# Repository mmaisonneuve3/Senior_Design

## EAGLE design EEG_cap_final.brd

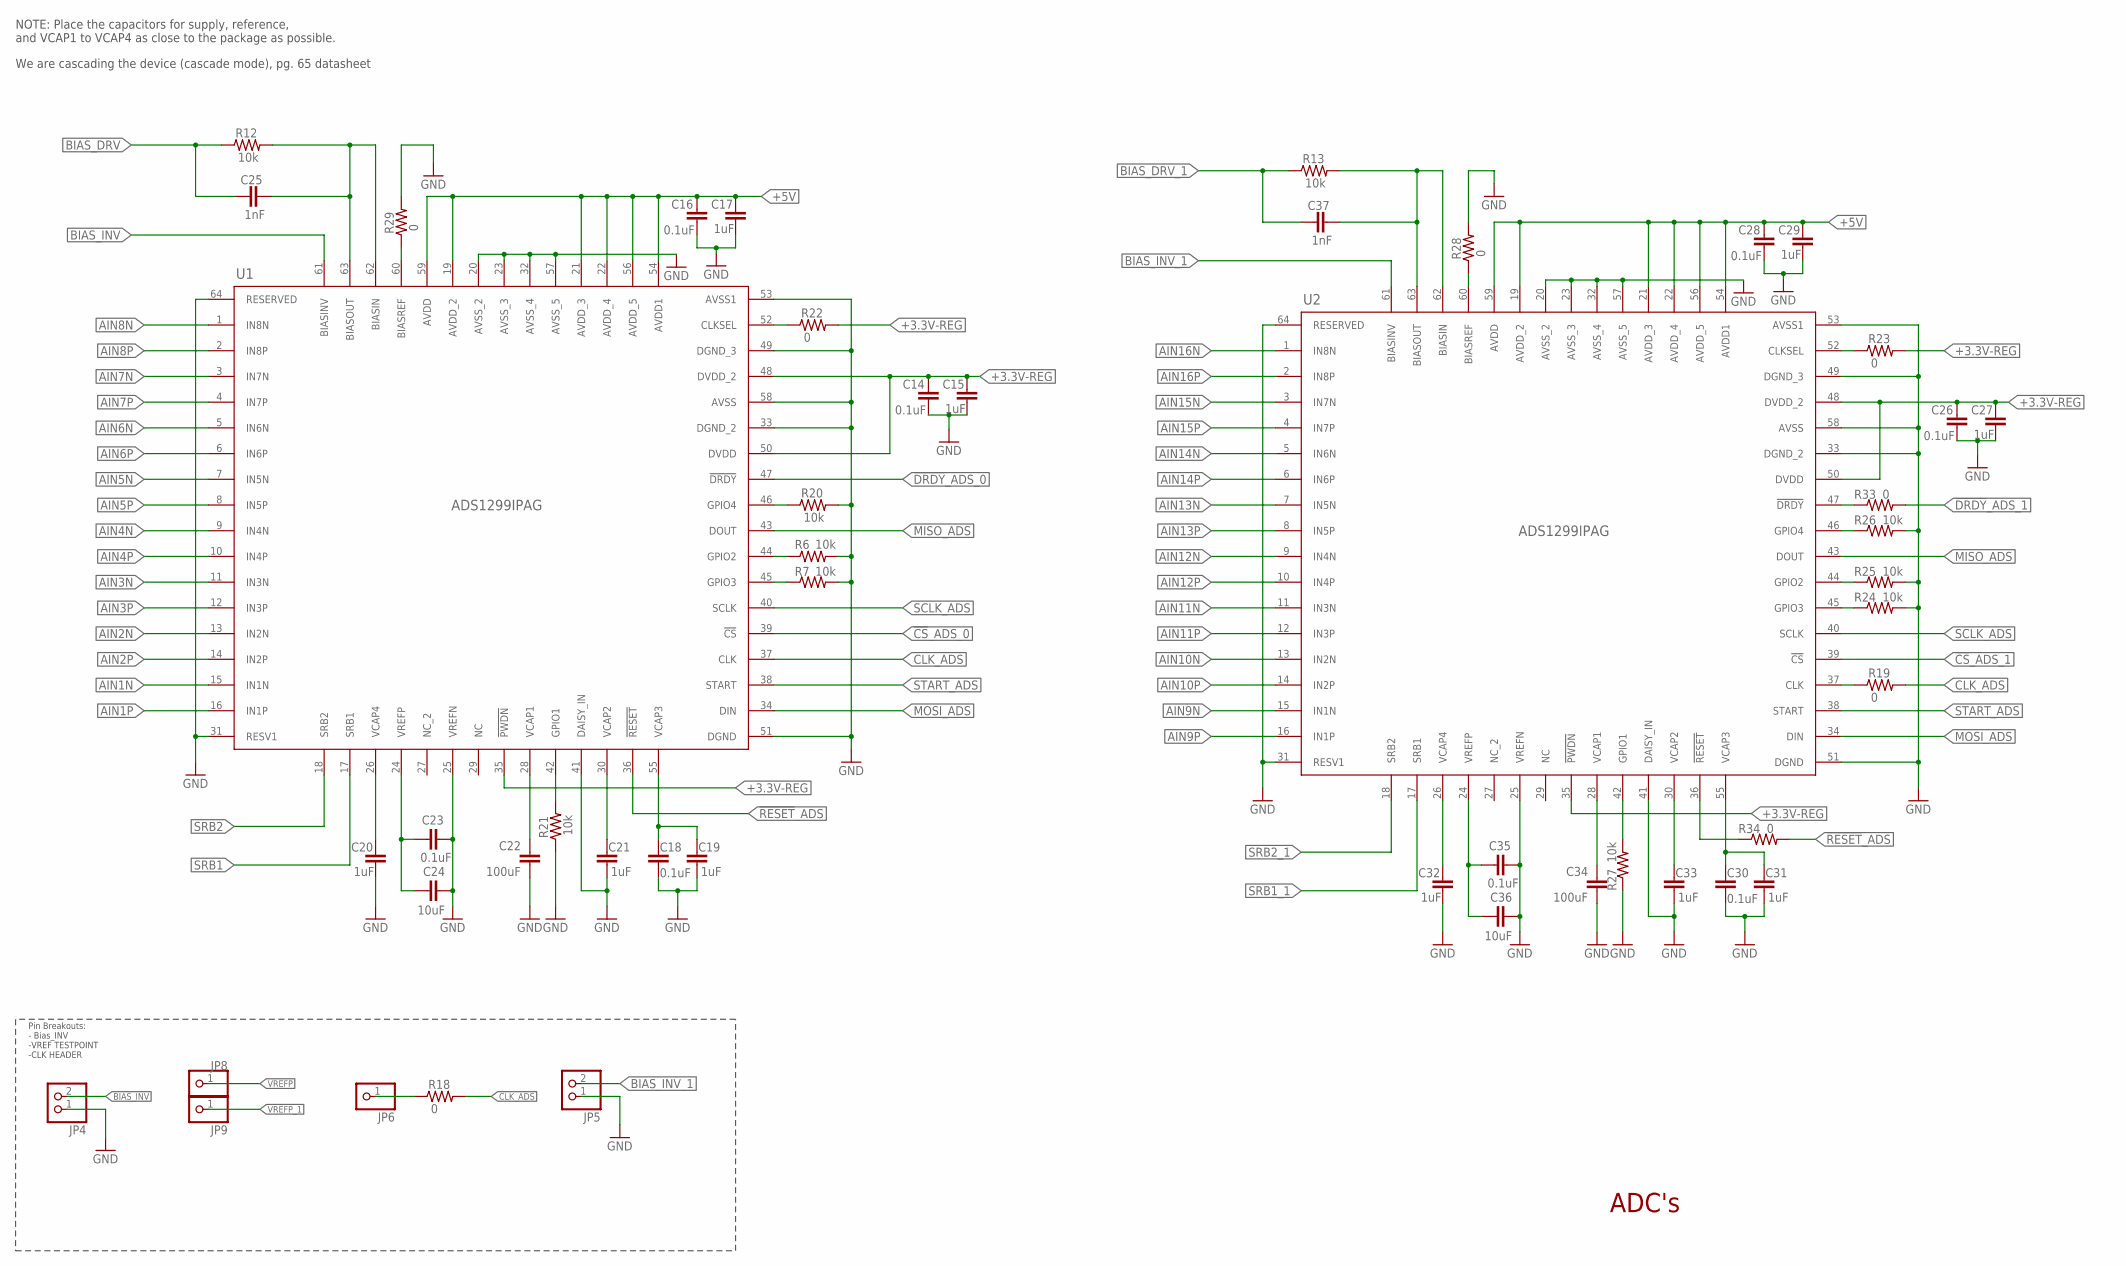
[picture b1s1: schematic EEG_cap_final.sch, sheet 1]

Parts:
C14, C16, C18, C23, C26, C28, C30, C35: 0.1uF; C0603
C15, C17, C19, C20, C21, C27, C29, C31, C32, C33: 1uF; C0603
C22, C34: 100uF; C1210
C24, C36: 10uF; C0805
C25, C37: 1nF; C0603
JP4, JP5: PINHD-1X2; 1X02
JP6, JP8, JP9: PINHD-1X1; 1X01
R6, R7, R12, R13, R20, R21, R24, R25, R26, R27: 10k; R0805
R18, R19, R22, R23, R28, R29, R33, R34: 0; R0805
U1, U2: ADS1299IPAG; PAG64_TEX

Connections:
!CS!_ADS_0: U1.39 (!CS); also elsewhere on the board
!CS!_ADS_1: U2.39 (!CS); also elsewhere on the board
!DRDY!_1: R33.1, U2.47 (!DRDY)
!DRDY!_ADS_0: U1.47 (!DRDY); also elsewhere on the board
!DRDY!_ADS_1: R33.2; also elsewhere on the board
!RESET!_ADS: R34.2, U1.36 (!RESET); also elsewhere on the board
!RESET!_ADS_1: R34.1, U2.36 (!RESET)
+3.3V-REG: C14.1, C15.1, C26.1, C27.1, R22.2, R23.2, U1.35 (!PWDN), U1.48 (DVDD_2), U1.50 (DVDD), U2.35 (!PWDN), U2.48 (DVDD_2), U2.50 (DVDD); also elsewhere on the board
+5V: C16.1, C17.1, C28.1, C29.1, U1.19 (AVDD_2), U1.21 (AVDD_3), U1.22 (AVDD_4), U1.54 (AVDD1), U1.56 (AVDD_5), U1.59 (AVDD), U2.19 (AVDD_2), U2.21 (AVDD_3), U2.22 (AVDD_4), U2.54 (AVDD1), U2.56 (AVDD_5), U2.59 (AVDD); also elsewhere on the board
AIN1N: U1.15 (IN1N); also elsewhere on the board
AIN1P: U1.16 (IN1P); also elsewhere on the board
AIN2N: U1.13 (IN2N); also elsewhere on the board
AIN2P: U1.14 (IN2P); also elsewhere on the board
AIN3N: U1.11 (IN3N); also elsewhere on the board
AIN3P: U1.12 (IN3P); also elsewhere on the board
AIN4N: U1.9 (IN4N); also elsewhere on the board
AIN4P: U1.10 (IN4P); also elsewhere on the board
AIN5N: U1.7 (IN5N); also elsewhere on the board
AIN5P: U1.8 (IN5P); also elsewhere on the board
AIN6N: U1.5 (IN6N); also elsewhere on the board
AIN6P: U1.6 (IN6P); also elsewhere on the board
AIN7N: U1.3 (IN7N); also elsewhere on the board
AIN7P: U1.4 (IN7P); also elsewhere on the board
AIN8N: U1.1 (IN8N); also elsewhere on the board
AIN8P: U1.2 (IN8P); also elsewhere on the board
AIN9N: U2.15 (IN1N); also elsewhere on the board
AIN9P: U2.16 (IN1P); also elsewhere on the board
AIN10N: U2.13 (IN2N); also elsewhere on the board
AIN10P: U2.14 (IN2P); also elsewhere on the board
AIN11N: U2.11 (IN3N); also elsewhere on the board
AIN11P: U2.12 (IN3P); also elsewhere on the board
AIN12N: U2.9 (IN4N); also elsewhere on the board
AIN12P: U2.10 (IN4P); also elsewhere on the board
AIN13N: U2.7 (IN5N); also elsewhere on the board
AIN13P: U2.8 (IN5P); also elsewhere on the board
AIN14N: U2.5 (IN6N); also elsewhere on the board
AIN14P: U2.6 (IN6P); also elsewhere on the board
AIN15N: U2.3 (IN7N); also elsewhere on the board
AIN15P: U2.4 (IN7P); also elsewhere on the board
AIN16N: U2.1 (IN8N); also elsewhere on the board
AIN16P: U2.2 (IN8P); also elsewhere on the board
BIAS1_IN: C37.2, R13.2, U2.62 (BIASIN), U2.63 (BIASOUT)
BIAS_DRV: C25.1, R12.1; also elsewhere on the board
BIAS_DRV_1: C37.1, R13.1; also elsewhere on the board
BIAS_IN: C25.2, R12.2, U1.62 (BIASIN), U1.63 (BIASOUT)
BIAS_INV: JP4.2, U1.61 (BIASINV)
BIAS_INV_1: JP5.2, U2.61 (BIASINV)
BIAS_REF: R29.1, U1.60 (BIASREF)
BIAS_REF_1: R28.1, U2.60 (BIASREF)
CLK: R19.1, U2.37 (CLK)
CLKSEL_0: R22.1, U1.52 (CLKSEL)
CLKSEL_1: R23.1, U2.52 (CLKSEL)
CLK_ADS: R18.2, R19.2, U1.37 (CLK)
CLK_HDR: JP6.1, R18.1
GND: C14.2, C15.2, C16.2, C17.2, C18.2, C19.2, C20.2, C21.2, C22.2, C23.2, C24.2, C26.2, C27.2, C28.2, C29.2, C30.2, C31.2, C32.2, C33.2, C34.2, C35.2, C36.2, JP4.1, JP5.1, R6.2, R7.2, R20.2, R21.1, R24.2, R25.2, R26.2, R27.1, R28.2, R29.2, U1.20 (AVSS_2), U1.23 (AVSS_3), U1.25 (VREFN), U1.31 (RESV1), U1.32 (AVSS_4), U1.33 (DGND_2), U1.41 (DAISY_IN), U1.49 (DGND_3), U1.51 (DGND), U1.53 (AVSS1), U1.57 (AVSS_5), U1.58 (AVSS), U1.64 (RESERVED), U2.20 (AVSS_2), U2.23 (AVSS_3), U2.25 (VREFN), U2.31 (RESV1), U2.32 (AVSS_4), U2.33 (DGND_2), U2.41 (DAISY_IN), U2.49 (DGND_3), U2.51 (DGND), U2.53 (AVSS1), U2.57 (AVSS_5), U2.58 (AVSS), U2.64 (RESERVED); also elsewhere on the board
MISO_ADS: U1.43 (DOUT), U2.43 (DOUT); also elsewhere on the board
MOSI_ADS: U1.34 (DIN), U2.34 (DIN); also elsewhere on the board
unnamed: R21.2, U1.42 (GPIO1)
unnamed: R7.1, U1.45 (GPIO3)
unnamed: R6.1, U1.44 (GPIO2)
unnamed: R20.1, U1.46 (GPIO4)
unnamed: R24.1, U2.45 (GPIO3)
unnamed: R25.1, U2.44 (GPIO2)
unnamed: R26.1, U2.46 (GPIO4)
unnamed: R27.2, U2.42 (GPIO1)
SCLK_ADS: U1.40 (SCLK), U2.40 (SCLK); also elsewhere on the board
SRB1: U1.17 (SRB1); also elsewhere on the board
SRB1_1: U2.17 (SRB1); also elsewhere on the board
SRB2: U1.18 (SRB2); also elsewhere on the board
SRB2_1: U2.18 (SRB2); also elsewhere on the board
START_ADS: U1.38 (START), U2.38 (START); also elsewhere on the board
VCAP1: C22.1, U1.28 (VCAP1)
VCAP1_1: C34.1, U2.28 (VCAP1)
VCAP2: C21.1, U1.30 (VCAP2)
VCAP2_1: C33.1, U2.30 (VCAP2)
VCAP3: C18.1, C19.1, U1.55 (VCAP3)
VCAP3_1: C30.1, C31.1, U2.55 (VCAP3)
VCAP4: C20.1, U1.26 (VCAP4)
VCAP6: C32.1, U2.26 (VCAP4)
VREFP: C23.1, C24.1, JP8.1, U1.24 (VREFP)
VREFP_1: C35.1, C36.1, JP9.1, U2.24 (VREFP)

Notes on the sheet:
ADC's
NOTE: Place the capacitors for supply, reference, and VCAP1 to VCAP4 as close to the package as possible.
We are cascading the device (cascade mode), pg. 65 datasheet
Pin Breakouts: - Bias_INV -VREF TESTPOINT -CLK HEADER

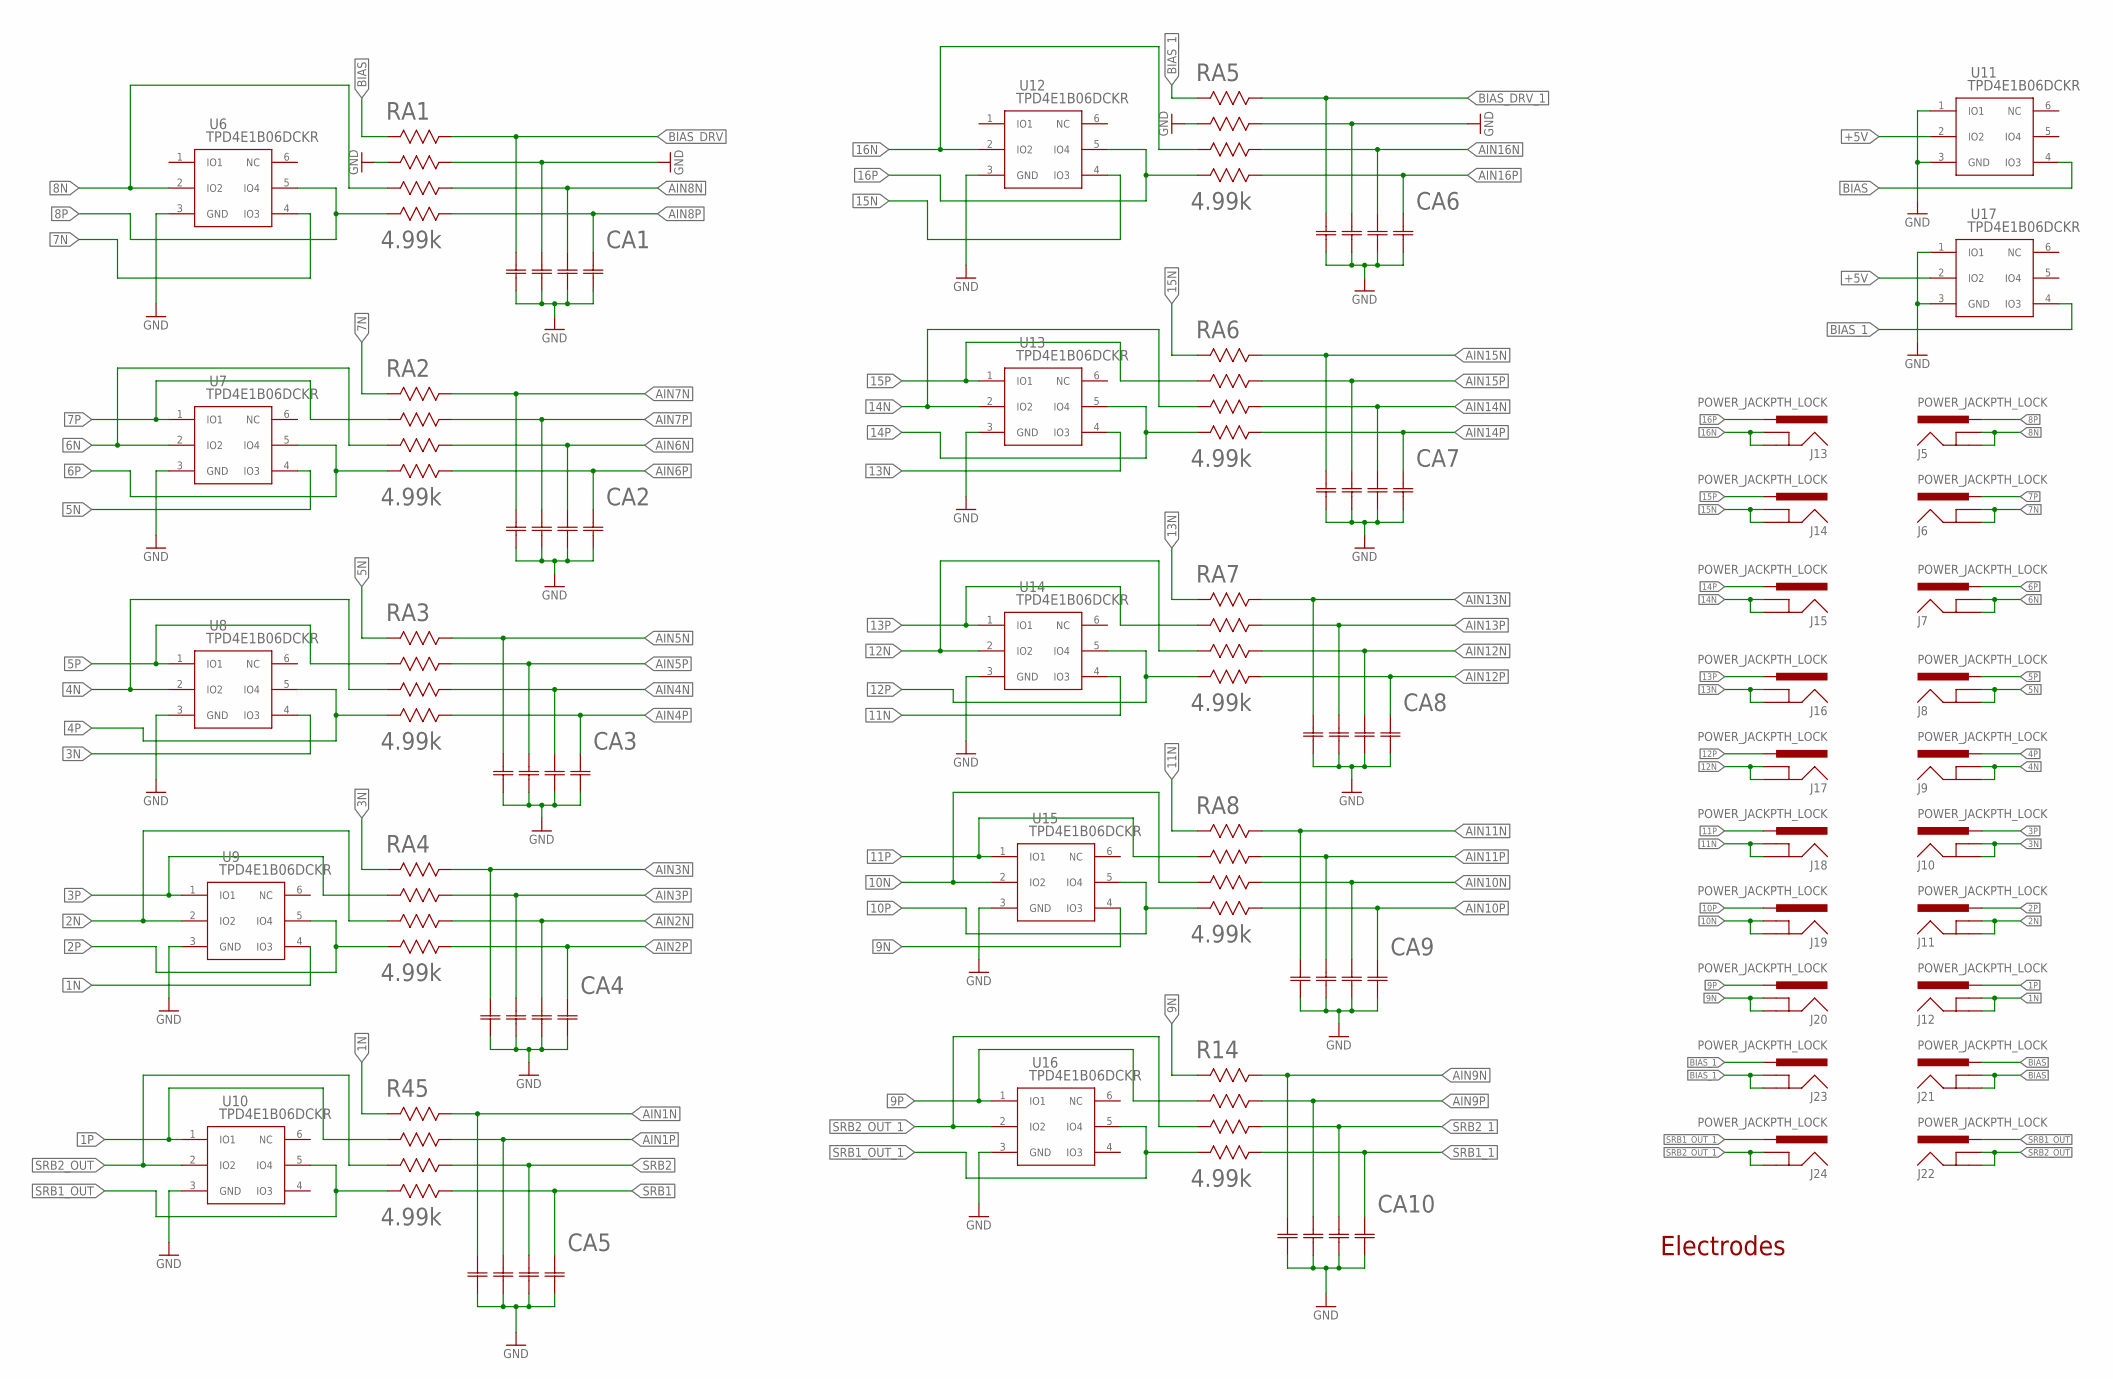
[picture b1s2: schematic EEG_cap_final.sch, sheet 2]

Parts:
CA1, CA2, CA3, CA4, CA5, CA6, CA7, CA8, CA9, CA10: 4.7nF; CAP_CA0612_3P2X1P6_YAG
J5, J6, J7, J8, J9, J10, J11, J12, J13, J14, J15, J16, J17, J18, J19, J20, J21, J22, J23, J24: POWER_JACKPTH_LOCK; POWER_JACK_PTH_LOCK
R14, R45: 4.99k; BO_CAT16
RA1, RA2, RA3, RA4, RA5, RA6, RA7, RA8: 4.99k; BO_CAT16
U6, U7, U8, U9, U10, U11, U12, U13, U14, U15, U16, U17: TPD4E1B06DCKR; DCK6_TEX

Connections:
1N: J12.GND, J12.GNDBREAK, R45.1, U9.4 (IO3)
1P: J12.PWR, R45.2, U10.1 (IO1)
2N: J11.GND, J11.GNDBREAK, RA4.3, U9.2 (IO2)
2P: J11.PWR, RA4.4, U9.5 (IO4)
3N: J10.GND, J10.GNDBREAK, RA4.1, U8.4 (IO3)
3P: J10.PWR, RA4.2, U9.1 (IO1)
4N: J9.GND, J9.GNDBREAK, RA3.3, U8.2 (IO2)
4P: J9.PWR, RA3.4, U8.5 (IO4)
5N: J8.GND, J8.GNDBREAK, RA3.1, U7.4 (IO3)
5P: J8.PWR, RA3.2, U8.1 (IO1)
6N: J7.GND, J7.GNDBREAK, RA2.3, U7.2 (IO2)
6P: J7.PWR, RA2.4, U7.5 (IO4)
7N: J6.GND, J6.GNDBREAK, RA2.1, U6.4 (IO3)
7P: J6.PWR, RA2.2, U7.1 (IO1)
8N: J5.GND, J5.GNDBREAK, RA1.3, U6.2 (IO2)
8P: J5.PWR, RA1.4, U6.5 (IO4)
9N: J20.GND, J20.GNDBREAK, R14.1, U15.4 (IO3)
9P: J20.PWR, R14.2, U16.1 (IO1)
10N: J19.GND, J19.GNDBREAK, RA8.3, U15.2 (IO2)
10P: J19.PWR, RA8.4, U15.5 (IO4)
11N: J18.GND, J18.GNDBREAK, RA8.1, U14.4 (IO3)
11P: J18.PWR, RA8.2, U15.1 (IO1)
12N: J17.GND, J17.GNDBREAK, RA7.3, U14.2 (IO2)
12P: J17.PWR, RA7.4, U14.5 (IO4)
13N: J16.GND, J16.GNDBREAK, RA7.1, U13.4 (IO3)
13P: J16.PWR, RA7.2, U14.1 (IO1)
14N: J15.GND, J15.GNDBREAK, RA6.3, U13.2 (IO2)
14P: J15.PWR, RA6.4, U13.5 (IO4)
15N: J14.GND, J14.GNDBREAK, RA6.1, U12.4 (IO3)
15P: J14.PWR, RA6.2, U13.1 (IO1)
16N: J13.GND, J13.GNDBREAK, RA5.3, U12.2 (IO2)
16P: J13.PWR, RA5.4, U12.5 (IO4)
+5V: U11.2 (IO2), U17.2 (IO2); also elsewhere on the board
AIN1N: CA5.8, R45.8; also elsewhere on the board
AIN1P: CA5.7, R45.7; also elsewhere on the board
AIN2N: CA4.6, RA4.6; also elsewhere on the board
AIN2P: CA4.5, RA4.5; also elsewhere on the board
AIN3N: CA4.8, RA4.8; also elsewhere on the board
AIN3P: CA4.7, RA4.7; also elsewhere on the board
AIN4N: CA3.6, RA3.6; also elsewhere on the board
AIN4P: CA3.5, RA3.5; also elsewhere on the board
AIN5N: CA3.8, RA3.8; also elsewhere on the board
AIN5P: CA3.7, RA3.7; also elsewhere on the board
AIN6N: CA2.6, RA2.6; also elsewhere on the board
AIN6P: CA2.5, RA2.5; also elsewhere on the board
AIN7N: CA2.8, RA2.8; also elsewhere on the board
AIN7P: CA2.7, RA2.7; also elsewhere on the board
AIN8N: CA1.6, RA1.6; also elsewhere on the board
AIN8P: CA1.5, RA1.5; also elsewhere on the board
AIN9N: CA10.8, R14.8; also elsewhere on the board
AIN9P: CA10.7, R14.7; also elsewhere on the board
AIN10N: CA9.6, RA8.6; also elsewhere on the board
AIN10P: CA9.5, RA8.5; also elsewhere on the board
AIN11N: CA9.8, RA8.8; also elsewhere on the board
AIN11P: CA9.7, RA8.7; also elsewhere on the board
AIN12N: CA8.6, RA7.6; also elsewhere on the board
AIN12P: CA8.5, RA7.5; also elsewhere on the board
AIN13N: CA8.8, RA7.8; also elsewhere on the board
AIN13P: CA8.7, RA7.7; also elsewhere on the board
AIN14N: CA7.6, RA6.6; also elsewhere on the board
AIN14P: CA7.5, RA6.5; also elsewhere on the board
AIN15N: CA7.8, RA6.8; also elsewhere on the board
AIN15P: CA7.7, RA6.7; also elsewhere on the board
AIN16N: CA6.6, RA5.6; also elsewhere on the board
AIN16P: CA6.5, RA5.5; also elsewhere on the board
BIAS: J21.GND, J21.GNDBREAK, J21.PWR, RA1.1, U11.4 (IO3)
BIAS_1: J23.GND, J23.GNDBREAK, J23.PWR, RA5.1, U17.4 (IO3)
BIAS_DRV: CA1.8, RA1.8; also elsewhere on the board
BIAS_DRV_1: CA6.8, RA5.8; also elsewhere on the board
GND: CA1.1, CA1.2, CA1.3, CA1.4, CA1.7, CA2.1, CA2.2, CA2.3, CA2.4, CA3.1, CA3.2, CA3.3, CA3.4, CA4.1, CA4.2, CA4.3, CA4.4, CA5.1, CA5.2, CA5.3, CA5.4, CA6.1, CA6.2, CA6.3, CA6.4, CA6.7, CA7.1, CA7.2, CA7.3, CA7.4, CA8.1, CA8.2, CA8.3, CA8.4, CA9.1, CA9.2, CA9.3, CA9.4, CA10.1, CA10.2, CA10.3, CA10.4, RA1.2, RA1.7, RA5.2, RA5.7, U6.3 (GND), U7.3 (GND), U8.3 (GND), U9.3 (GND), U10.3 (GND), U11.1 (IO1), U11.3 (GND), U12.3 (GND), U13.3 (GND), U14.3 (GND), U15.3 (GND), U16.3 (GND), U17.1 (IO1), U17.3 (GND); also elsewhere on the board
SRB1: CA5.5, R45.5; also elsewhere on the board
SRB1_1: CA10.5, R14.5; also elsewhere on the board
SRB1_OUT: J22.PWR, R45.4, U10.5 (IO4)
SRB1_OUT_1: J24.PWR, R14.4, U16.5 (IO4)
SRB2: CA5.6, R45.6; also elsewhere on the board
SRB2_1: CA10.6, R14.6; also elsewhere on the board
SRB2_OUT: J22.GND, J22.GNDBREAK, R45.3, U10.2 (IO2)
SRB2_OUT_1: J24.GND, J24.GNDBREAK, R14.3, U16.2 (IO2)

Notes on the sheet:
Electrodes

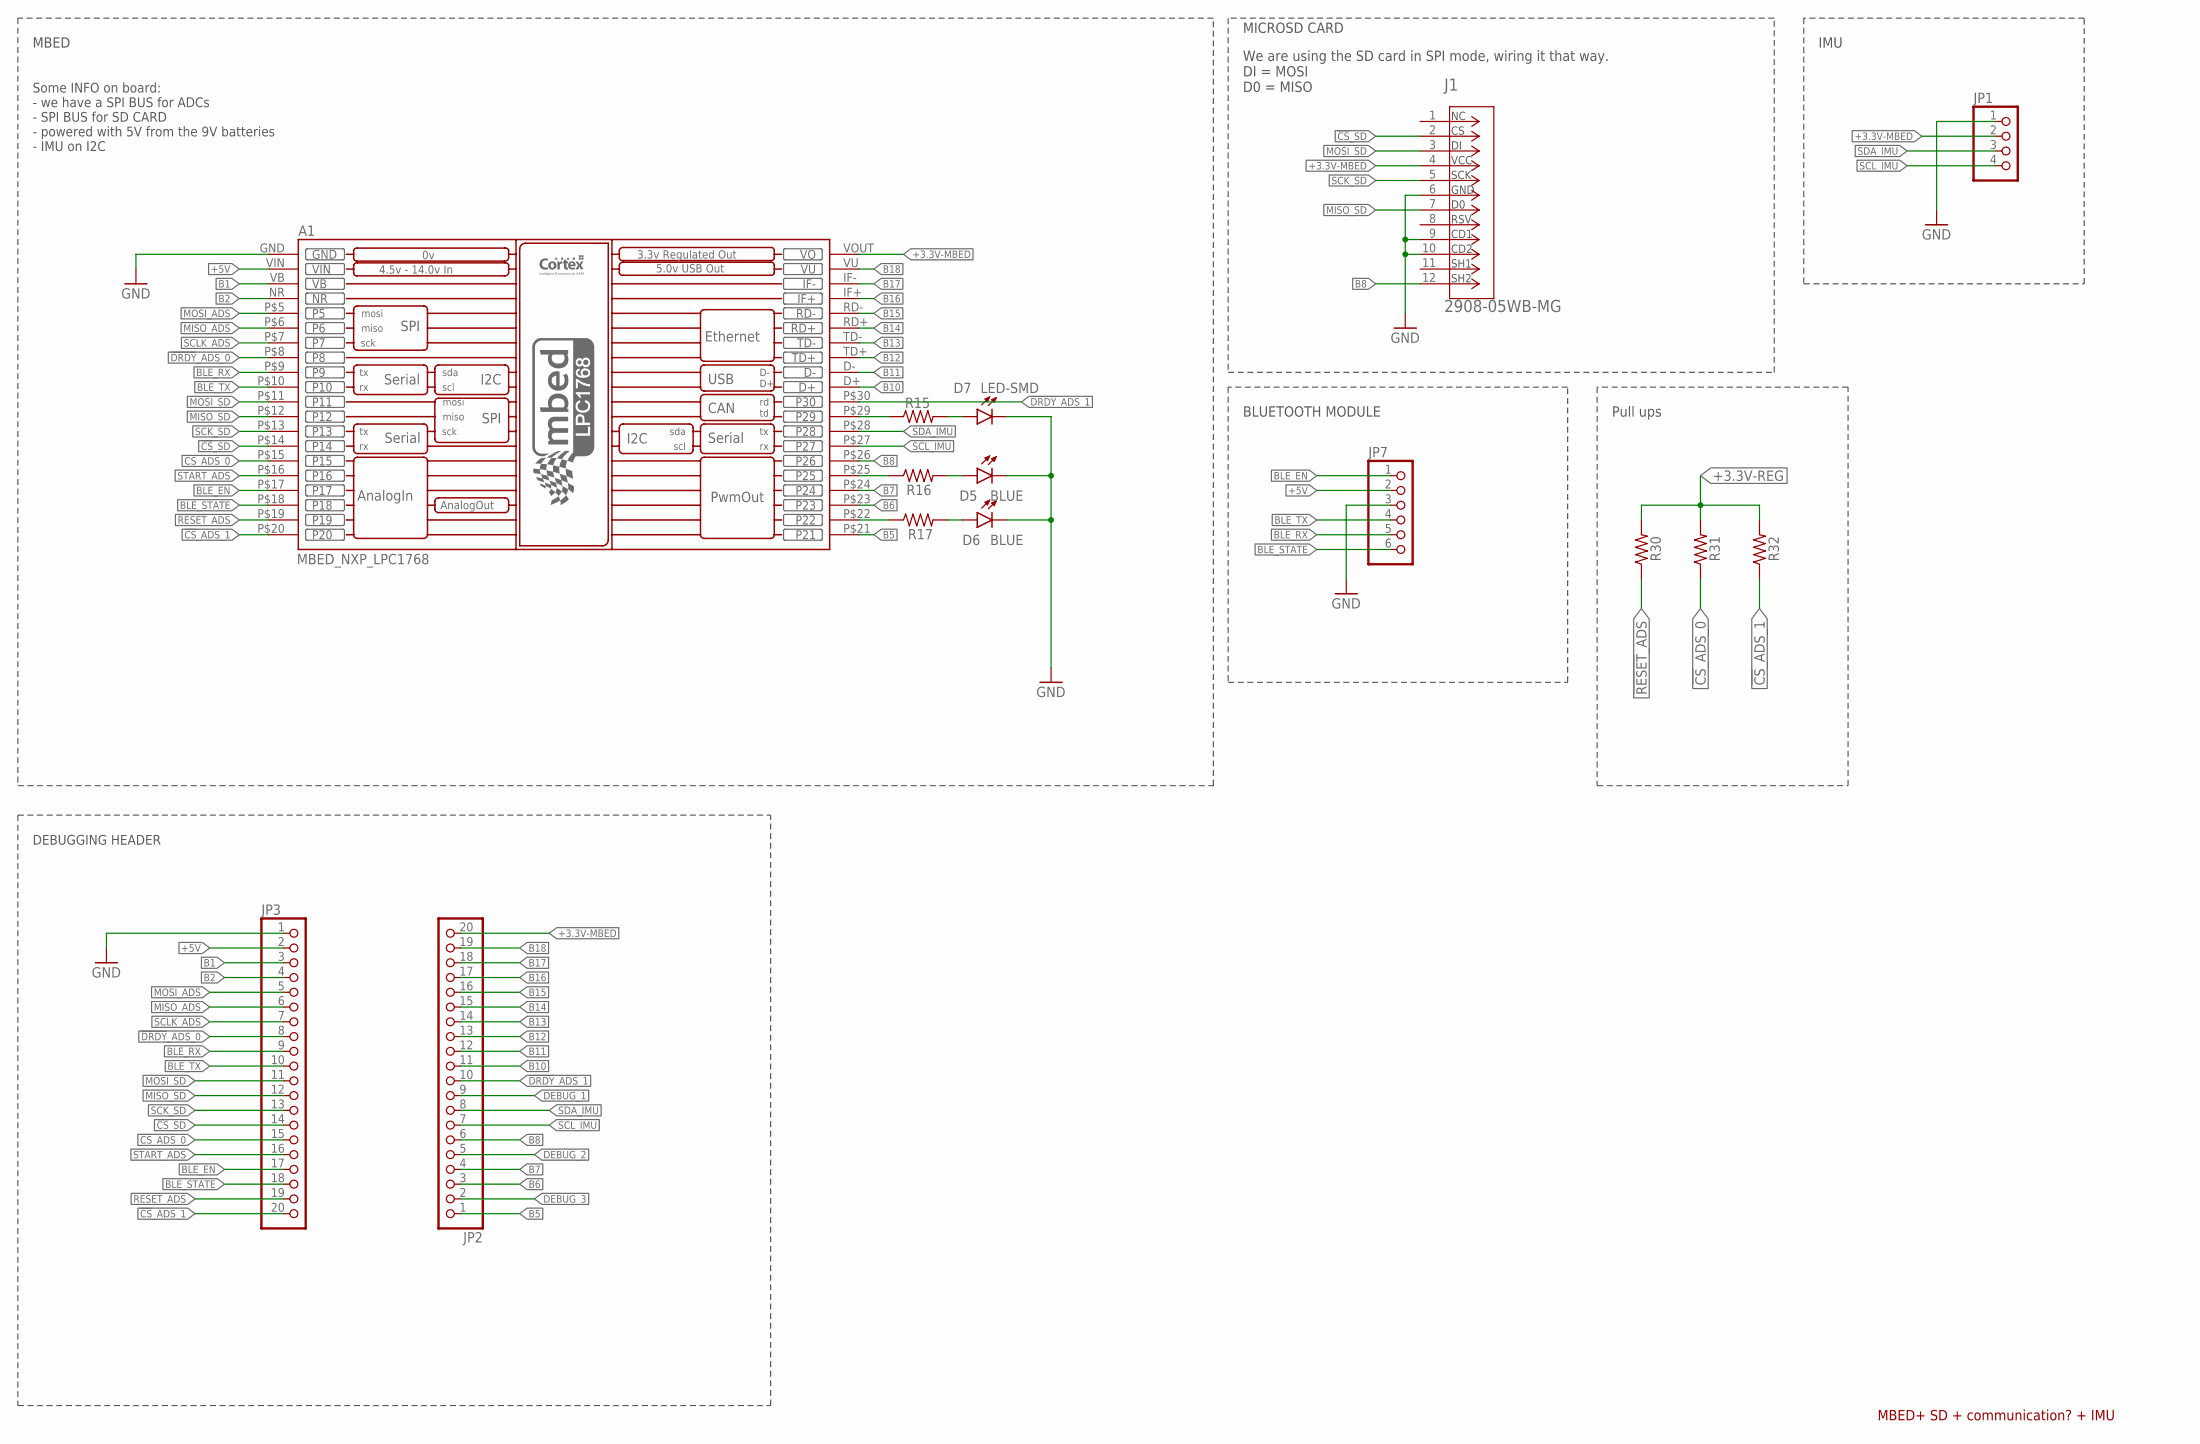
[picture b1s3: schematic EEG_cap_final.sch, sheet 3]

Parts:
A1: MBED_NXP_LPC1768; MBED_LPC1768
D5, D6: BLUE; LED0603
D7: LED-SMD; LED0603
J1: 2908-05WB-MG; CONN_3M_2900
JP1: PINHD-1X4; 1X04
JP2, JP3: PINHD-1X20; 1X20
JP7: PINHD-1X6; 1X06
R15, R16, R17, R31, R32: 1k; R0805
R30: 10k; R0805

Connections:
!CS!_ADS_0: A1.P$15 (P15), JP3.15, R31.1; also elsewhere on the board
!CS!_ADS_1: A1.P$20 (P20), JP3.20, R32.1; also elsewhere on the board
!CS!_SD: A1.P$14 (P14), J1.2, JP3.14
!DRDY!_ADS_0: A1.P$8 (P8), JP3.8; also elsewhere on the board
!DRDY!_ADS_1: A1.P$30 (P30), JP2.10; also elsewhere on the board
!RESET!_ADS: A1.P$19 (P19), JP3.19, R30.1; also elsewhere on the board
+3.3V-MBED: A1.VOUT (VO), J1.4, JP1.2, JP2.20; also elsewhere on the board
+3.3V-REG: R30.2, R31.2, R32.2; also elsewhere on the board
+5V: A1.VIN, JP3.2, JP7.2; also elsewhere on the board
B1: A1.VB, JP3.3
B2: A1.NR, JP3.4
B5: A1.P$21 (P21), JP2.1
B6: A1.P$23 (P23), JP2.3
B7: A1.P$24 (P24), JP2.4
B8: A1.P$26 (P26), J1.12, JP2.6
B10: A1.D+, JP2.11
B11: A1.D-, JP2.12
B12: A1.TD+, JP2.13
B13: A1.TD-, JP2.14
B14: A1.RD+, JP2.15
B15: A1.RD-, JP2.16
B16: A1.IF+, JP2.17
B17: A1.IF-, JP2.18
B18: A1.VU, JP2.19
BLE_EN: A1.P$17 (P17), JP3.17, JP7.1
BLE_RX: A1.P$9 (P9), JP3.9, JP7.5
BLE_STATE: A1.P$18 (P18), JP3.18, JP7.6
BLE_TX: A1.P$10 (P10), JP3.10, JP7.4
DEBUG_1: A1.P$29 (P29), JP2.9, R15.1
DEBUG_2: A1.P$25 (P25), JP2.5, R16.1
DEBUG_3: A1.P$22 (P22), JP2.2, R17.1
GND: A1.GND, D5.C, D6.C, D7.C, J1.6, J1.9, J1.10, JP1.1, JP3.1, JP7.3; also elsewhere on the board
LED-1: D7.A, R15.2
LED_2: D5.A, R16.2
LED_3: D6.A, R17.2
MISO_ADS: A1.P$6 (P6), JP3.6; also elsewhere on the board
MISO_SD: A1.P$12 (P12), J1.7, JP3.12
MOSI_ADS: A1.P$5 (P5), JP3.5; also elsewhere on the board
MOSI_SD: A1.P$11 (P11), J1.3, JP3.11
SCK_SD: A1.P$13 (P13), J1.5, JP3.13
SCLK_ADS: A1.P$7 (P7), JP3.7; also elsewhere on the board
SCL_IMU: A1.P$27 (P27), JP1.4, JP2.7
SDA_IMU: A1.P$28 (P28), JP1.3, JP2.8
START_ADS: A1.P$16 (P16), JP3.16; also elsewhere on the board

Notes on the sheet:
MBED+ SD + communication? + IMU
MBED
MICROSD CARD
We are using the SD card in SPI mode, wiring it that way. DI = MOSI D0 = MISO
Some INFO on board: - we have a SPI BUS for ADCs - SPI BUS for SD CARD - powered with 5V from the 9V batteries - IMU on I2C
IMU
DEBUGGING HEADER
BLUETOOTH MODULE
Pull ups

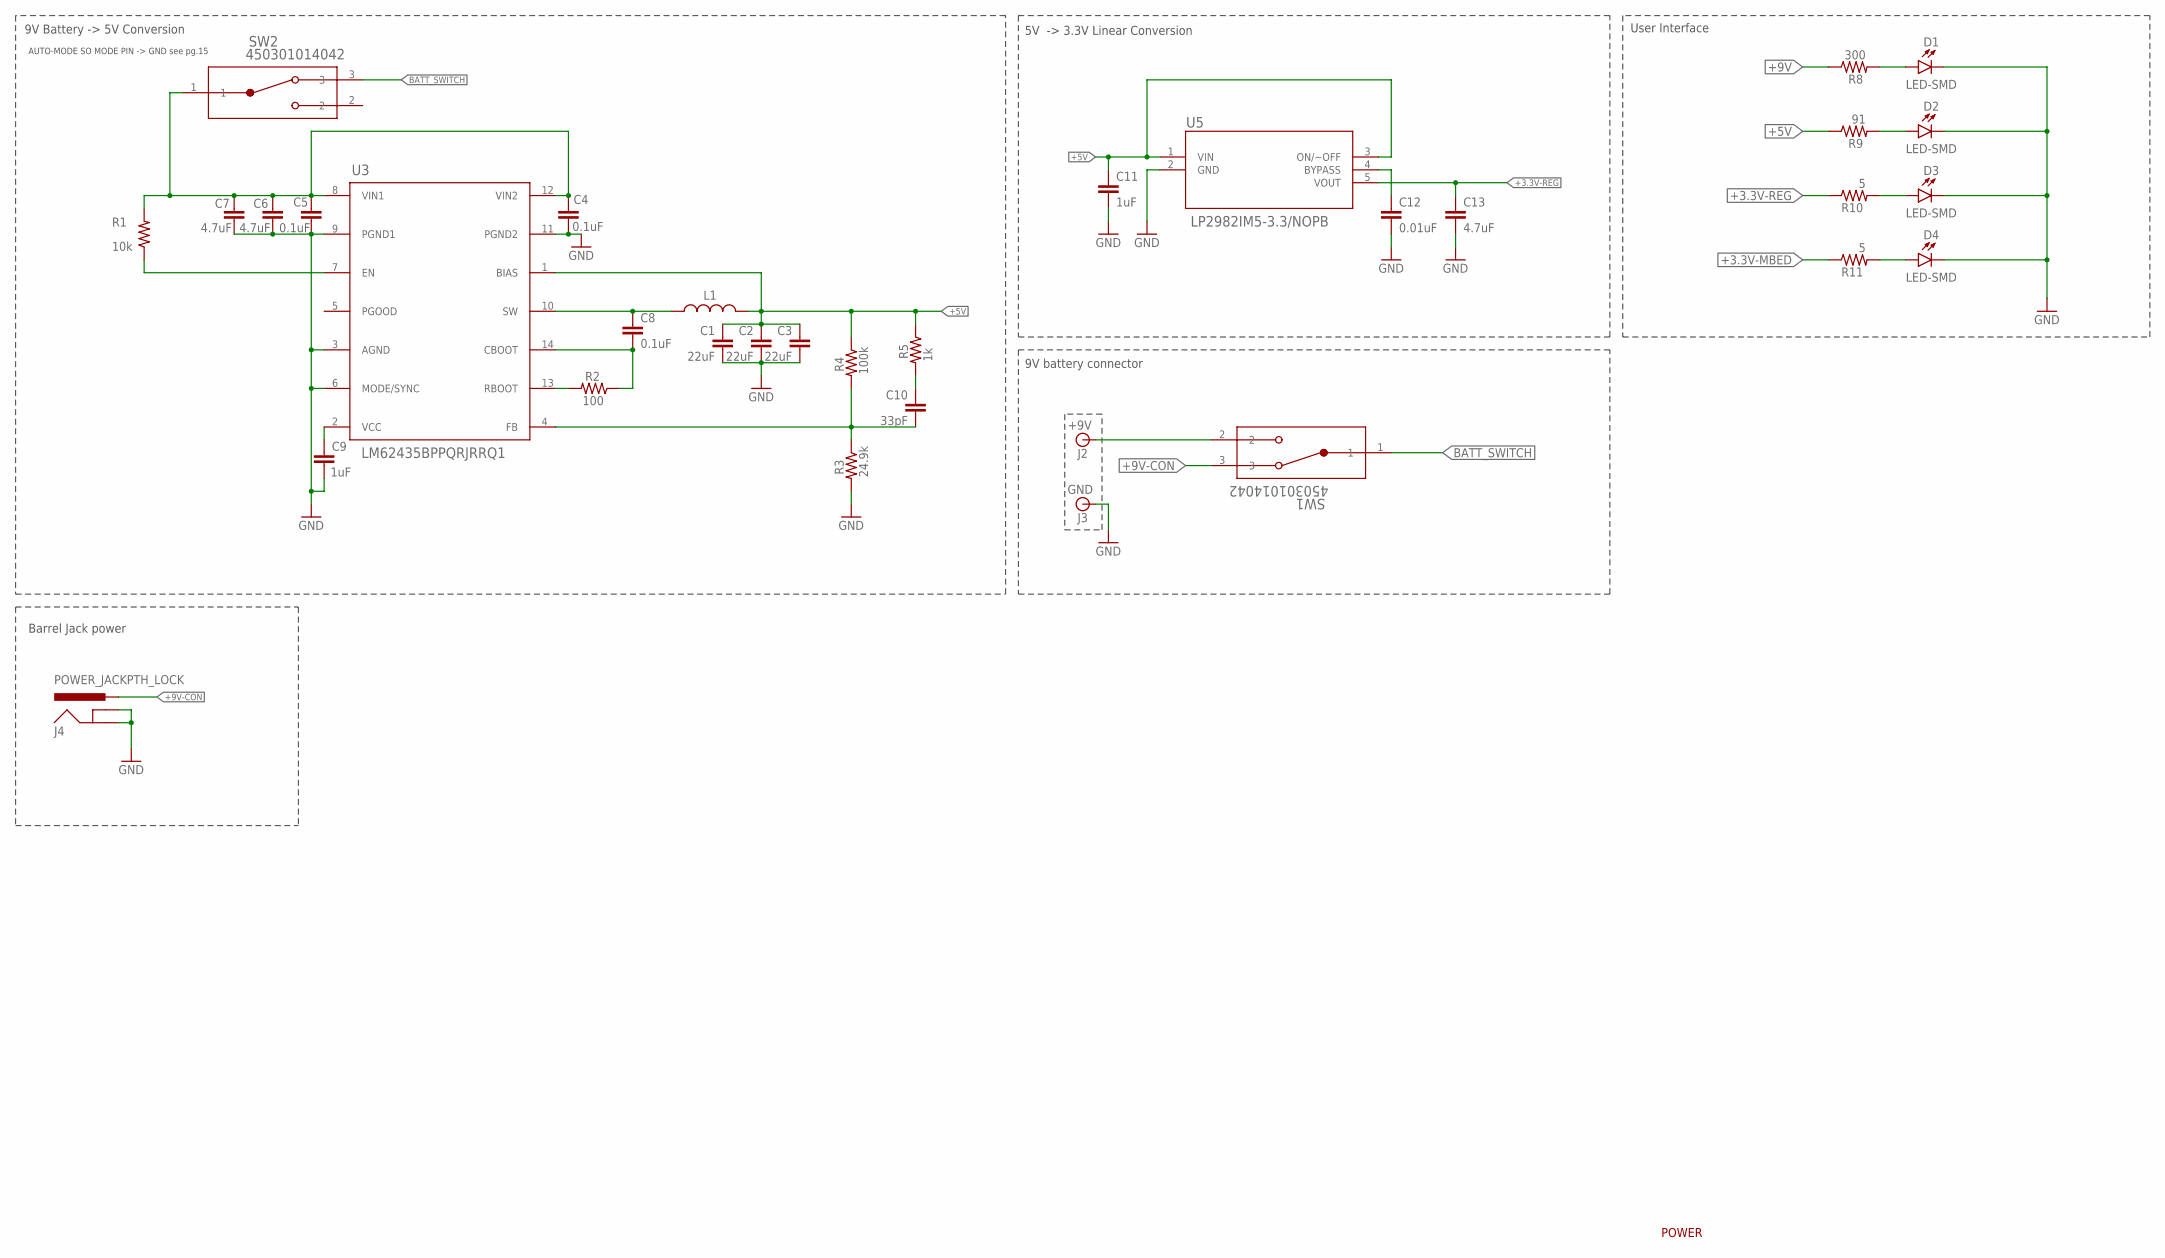
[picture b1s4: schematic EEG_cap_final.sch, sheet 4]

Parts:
C1, C2, C3: 22uF; C0805
C4, C5, C8: 0.1uF; C0805
C6, C7, C13: 4.7uF; C0805
C9, C11: 1uF; C0805
C10: 33pF; C0805
C12: 0.01uF; C0805
D1, D2, D3, D4: LED-SMD; LED0603
J2: +9V; BANANA_CONN
J3: GND; BANANA_CONN
J4: POWER_JACKPTH_LOCK; POWER_JACK_PTH_LOCK
L1: DFE252010P-1R5M=P2; INDC2520X100N
R1: 10k; R0805
R2: 100; R0805
R3: 24.9k; R0805
R4: 100k; R0805
R5: 1k; R0805
R8: 300; R0805
R9: 91; R0805
R10, R11: 5; R0805
SW1, SW2: 450301014042; SW_450301014042_WRE
U3: LM62435BPPQRJRRQ1; VQFN-HR14_RJR_TEX
U5: LP2982IM5-3.3/NOPB; MF05A

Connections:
3.3V_DIG_LED: D4.A, R11.2
3.3_ANA_LED: D3.A, R10.2
5V_LED: D2.A, R9.2
9V_LED: D1.A, R8.2
+3.3V-MBED: R11.1; also elsewhere on the board
+3.3V-REG: C13.1, R10.1, U5.5 (VOUT); also elsewhere on the board
+5V: C1.1, C2.1, C3.1, C11.1, L1.2, R4.1, R5.1, R9.1, U3.1 (BIAS), U5.1 (VIN), U5.3 (ON/~OFF); also elsewhere on the board
+9V: C4.1, C5.1, C6.1, C7.1, R1.2, R8.1, SW2.1, U3.8 (VIN1), U3.12 (VIN2)
+9V-CON: J4.PWR, SW1.3
+9V_BATT: J2.P$1, SW1.2
BATT_SWITCH: SW1.1, SW2.3
BYPASS: C12.1, U5.4 (BYPASS)
CBOOT: C8.2, R2.1, U3.14 (CBOOT)
EN: R1.1, U3.7 (EN)
FB: C10.2, R3.1, R4.2, U3.4 (FB)
FB_CAP: C10.1, R5.2
GND: C1.2, C2.2, C3.2, C4.2, C5.2, C6.2, C7.2, C9.2, C11.2, C12.2, C13.2, D1.C, D2.C, D3.C, D4.C, J3.P$1, J4.GND, J4.GNDBREAK, R3.2, U3.3 (AGND), U3.6 (MODE/SYNC), U3.9 (PGND1), U3.11 (PGND2), U5.2 (GND); also elsewhere on the board
RBOOT: R2.2, U3.13 (RBOOT)
SW: C8.1, L1.1, U3.10 (SW)
VCC_CHIP: C9.1, U3.2 (VCC)

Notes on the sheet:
POWER
9V Battery -> 5V Conversion
AUTO-MODE SO MODE PIN -> GND see pg.15
5V -> 3.3V Linear Conversion
9V battery connector
User Interface
Barrel Jack power

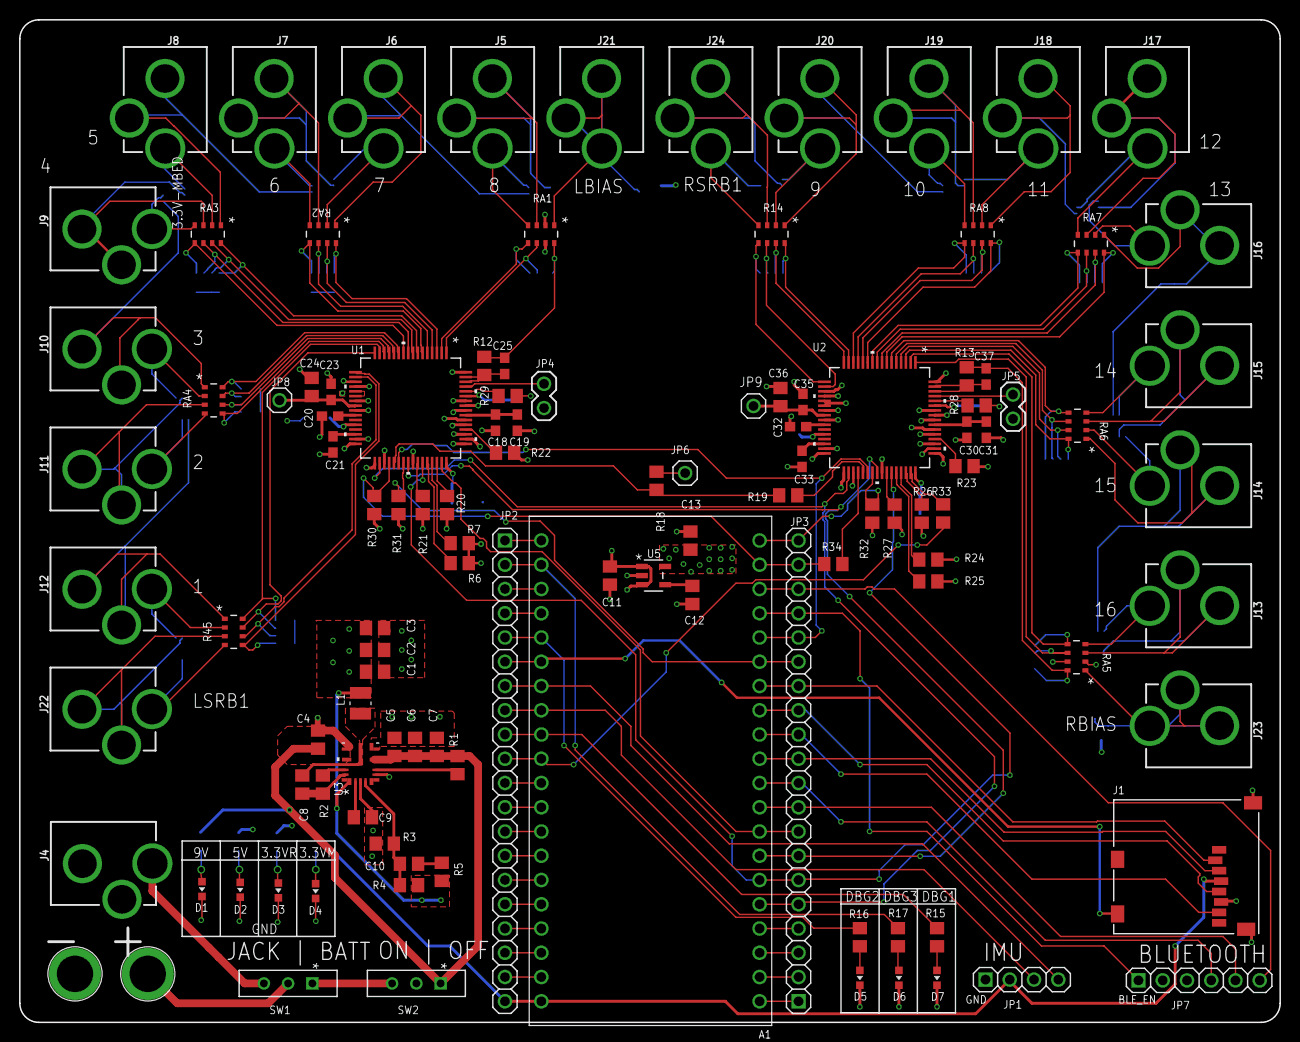
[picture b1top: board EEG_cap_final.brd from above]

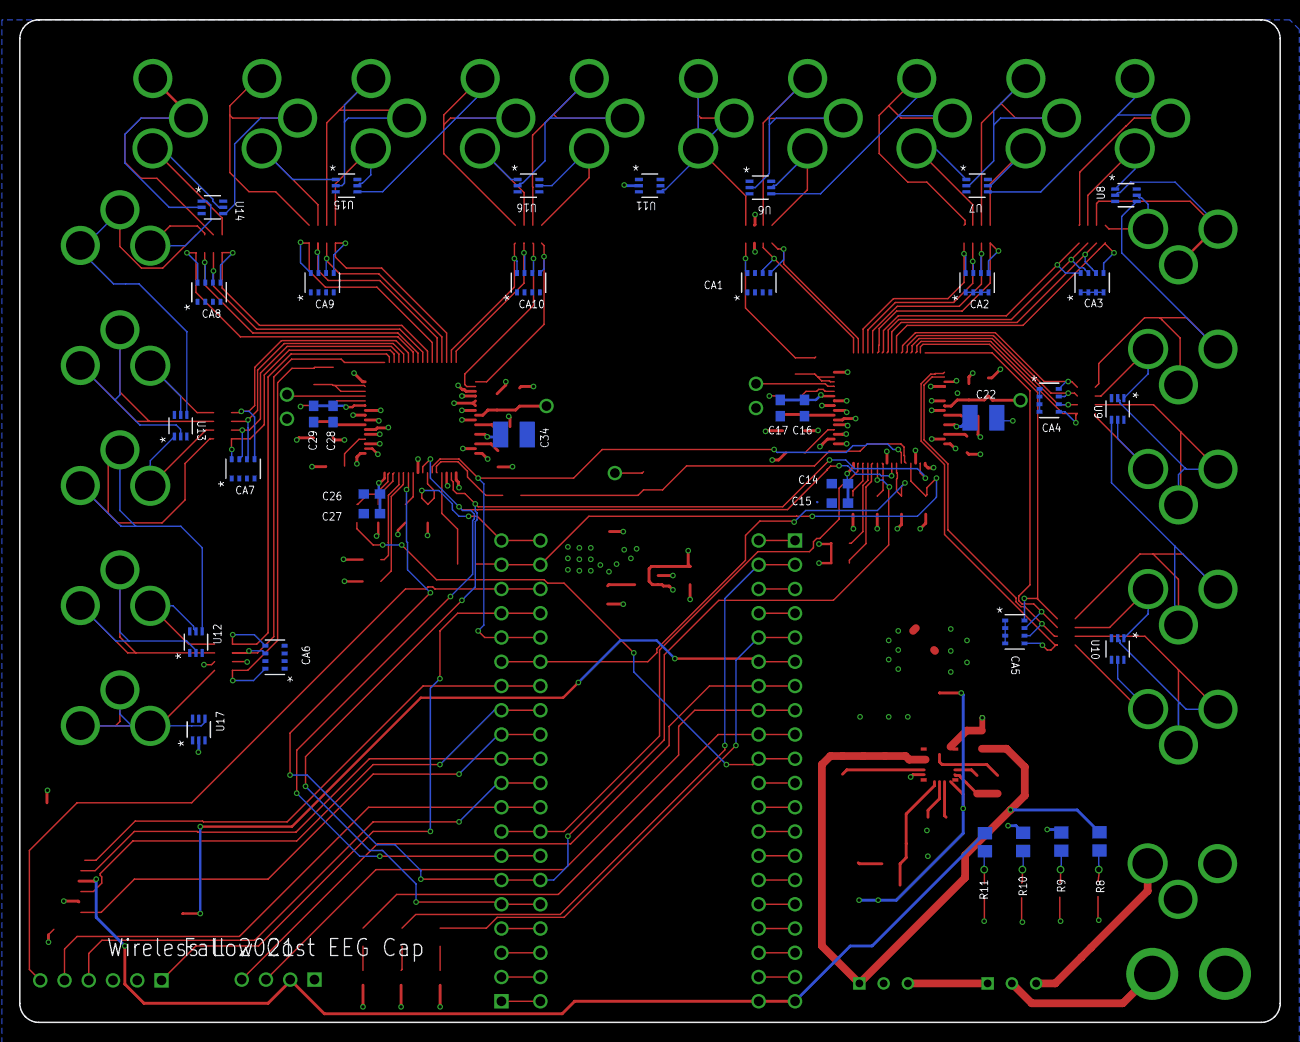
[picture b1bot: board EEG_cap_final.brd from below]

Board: 4 copper layers, 132.0 x 105.0 mm, 150 parts (36 on the bottom side), 167 nets.

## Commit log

2021-11-14 Add files via upload
    BoM

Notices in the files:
parts and their libraries:
SparkFun-Connectors: Licensing: Creative Commons ShareAlike 4.0 International - https://creativecommons.org/licenses/by-sa/4.0
COPYRIGHT: Copyright (C) 2021 Ultra Librarian. All rights reserved.
